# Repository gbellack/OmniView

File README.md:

#OmniView

##Hardware
--------
1. Texas Instruments CC3200 MCU

##Installation
1. You will need Code Composer Studio (CCS) version 6.1.1 installed on your computer. You can download this from TI's website. You will need to enter some credentials and get approved to be able to download the software.
2. You will be prompted to select modules that you want CCS to download. Please install the CC3200 package under SimpleLink Wifi Support tools.
3. After installing CCS, please install the CC3200 SDK from Texas Instruments.
4. If you launch Code Composer Studio for the first time, it will prompt you for a workspace directory. Feel free to pick a directory that you would like to work off.
5. Here comes the fun part. Please install GitHub for Windows. You will need this to pull the CCS project from this repository.  
// TODO

You should be able to build and run the project once all these are set up. 

###Flashing the program via UniFlash

If you would like to flash the program onto the Launchpad, you will need a seaparate program called Uniflash by Texas Instruments. Go ahead and download it from here and continue to follow the steps below. If you would not like to do so, you may skip them.
Credits to: [Texas Instruments Uniflash Wiki page](http://processors.wiki.ti.com/index.php/UniFlash_Quick_Start_Guide)

### Folder/File description
1. omniview/main.c : This is where the main program lies. All things related to scheduling is done here.

2. omniview/mode.c: This file contains the two modes that the facial recognition is capable of doing, as well as module initialization functions. All modules (display, camera etc.) are included and used here. Primary mode basically takes an image every second and returns the name of the person in the image.

3. omniview/pinmux.c/h : This is where we specify which pins are being used for certain protocols by the program.

4. omniview/modules folder: This stores all the modules/component libraries. More on that later...

5. omniview/modules/display/display.c/h: This file implements the driver for the display. It provides a good interface for the OLED display that we are using.

6. omniview/modules/display/buffer.c: This file contains the display buffer. The reason why we have this in a separate file is because the display had initialization values that we wanted to keep, and by adding this huge buffer definition in our display function, it will make that file really big and hard to read. Hence, we decided to split it into a separate file and link it up.

7. omniview/modules/display/font.c: This file contains the font settings for text on our OLED display. For the same reason above, we decided to move it to a separate file.

8. omniview/modules/interrupts/button_interrupt.c/h: These files contain interfaces for triggering a GPIO interrupt via one of our buttons. Some of the macros are linked to other macros defined by Texas Instruments.

9. omniview/modules/interrupts/timer_interrupt.c/h: These files contain interfaces for triggering a timer interrupt. This is mainly used by the microphone interface for audio recording purposes during secondary mode.

10. omniview/modules/microphone/microphone.c/h: These files contain the interfaces for the microphone.

11. omniview/modules/networking/tcp_network.c/h: These files contain the TCP networking interface required to send data/files across the network (or in our case, interact with our server).

12. omniview/modules/camera/mt9d111.c/h: These files contain the driver for the camera model that we are currently using.

13. omniview/modules/face_software/faceRec.cpp: This file contains the main server loop as well as several functions that help it in running.

14. omniview/modules/face_software/tcpClient.c/h: Houses the server side networking code used to communicate (by TCP) with the embedded device.

15. omniview/modules/face_software/wav_transcribe.py: Called by the main facial recognition loop. Communicates with google’s speech to text recognition server. Sends a string to parseName and receives names back. Sends names back to facial recognition main.

16. omniview/modules/face_software/parseName.py: Uses a natural language processing toolkit to process the string. Returns the names identified by the algorithm to wav_transcribe.

17. omniview/modules/face_software/training: Database holding our folders of faces. Test pic gets compared to this database to find the most similar face. A folder is created for each unique person in our dataset. The folder, named after the person, houses the pictures of the person inside.
Eg. omniview/modules/face_software/training/john_connolly/john1.jpg  is the first picture of John Connolly in the database.

###Speech Recognition
Please READ:
1. Make sure you have PyAudio installed.
2. All the examples are in the speech_recognition file.

###Version Control for Code Composer Studio Project
The .gitignore file on this repository should do the trick, but please:  
  
DO commit and push:  
1. .ccsproject  
2. .cproject  
3. .project  
4. .settings folder  
5. makefile.defs (if using SYS/BIOS)  

DO NOT commit and push:    
1. Release/*  
2. config/*  
3. .launches/  
4. .xdchelp  

Credits to: [Texas Instruments Wiki page](http://processors.wiki.ti.com/index.php/Source_control_with_CCS)  

##Support
Please feel free to contact any of us if you have any questions or concerns.

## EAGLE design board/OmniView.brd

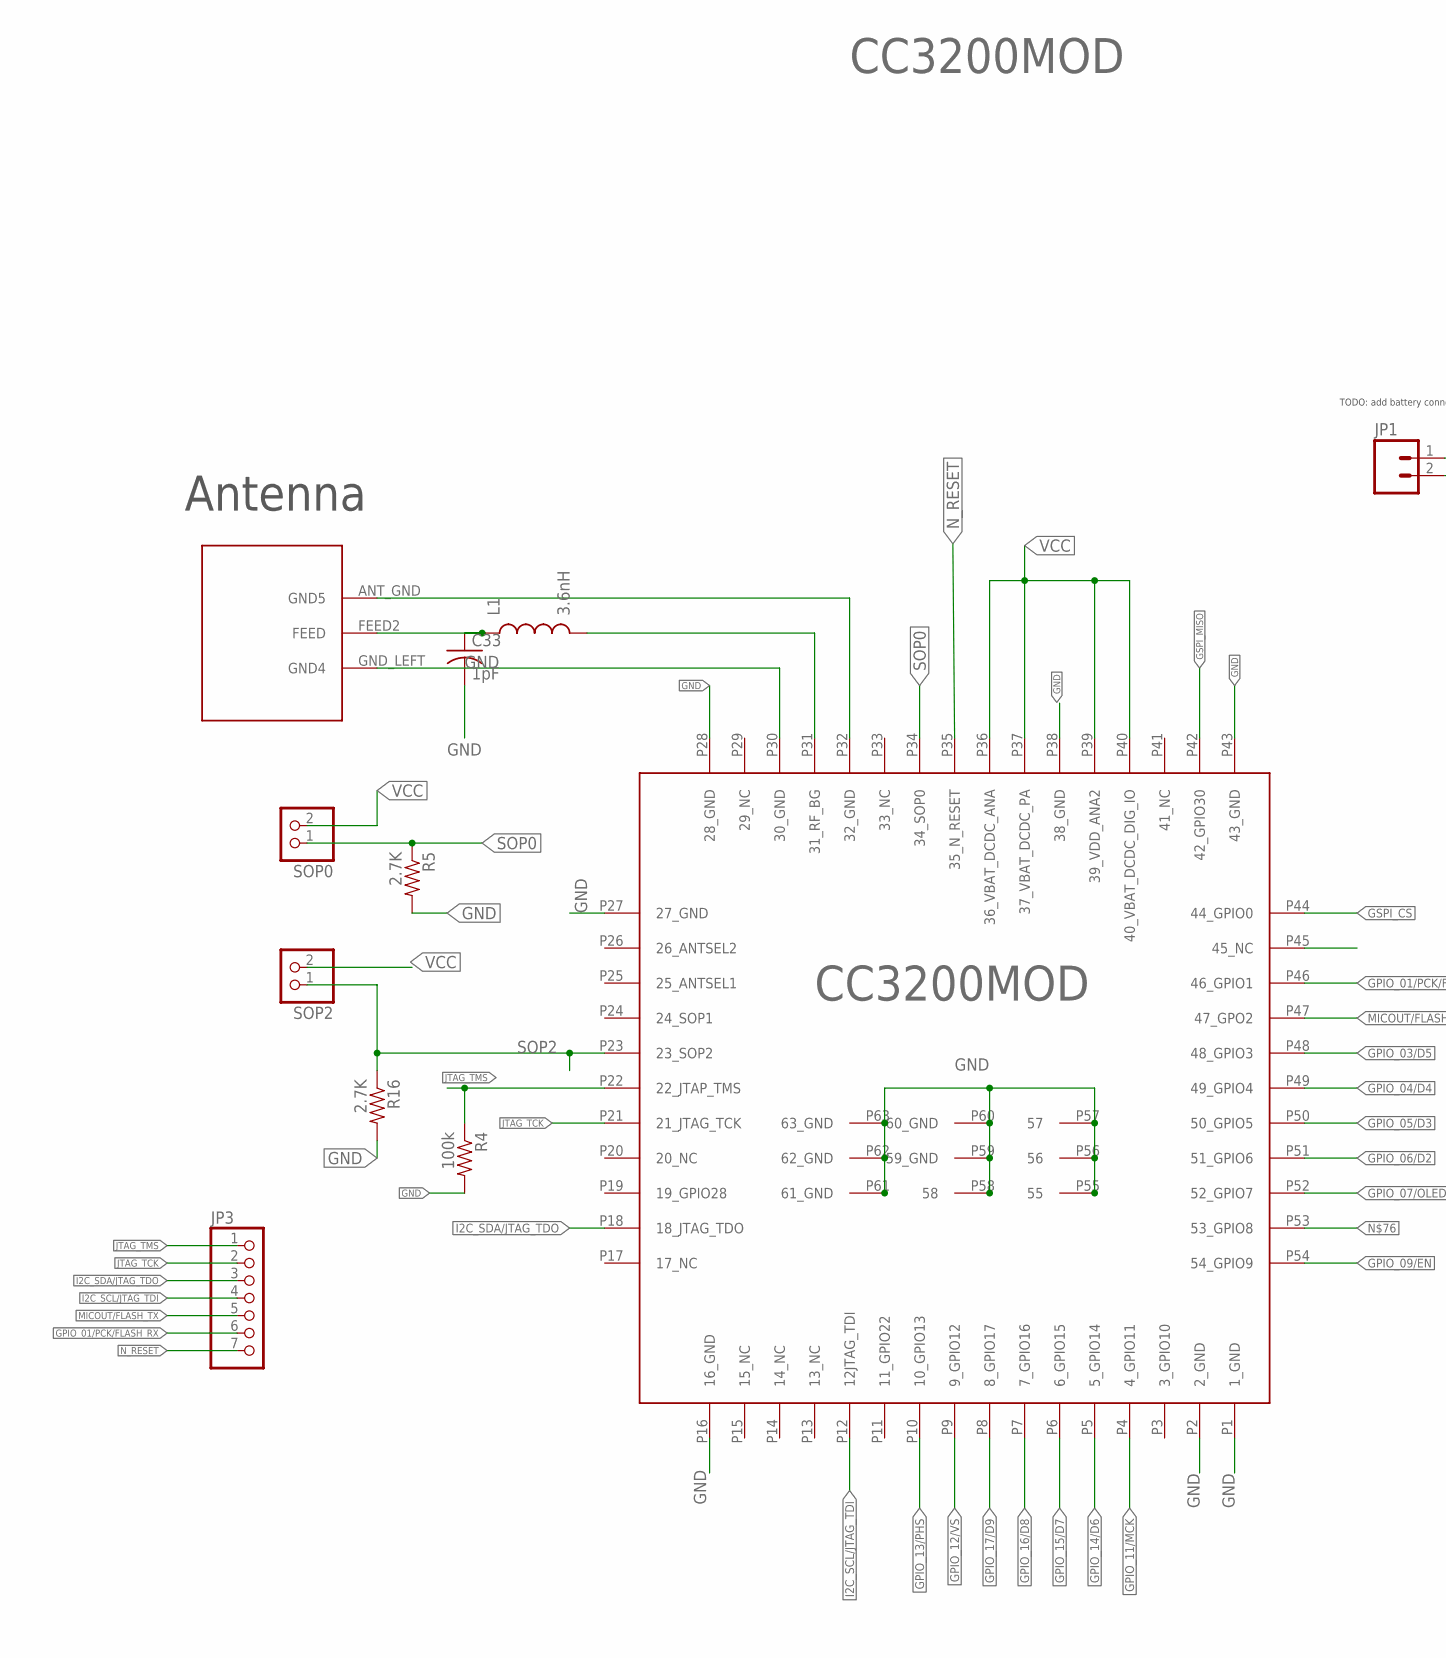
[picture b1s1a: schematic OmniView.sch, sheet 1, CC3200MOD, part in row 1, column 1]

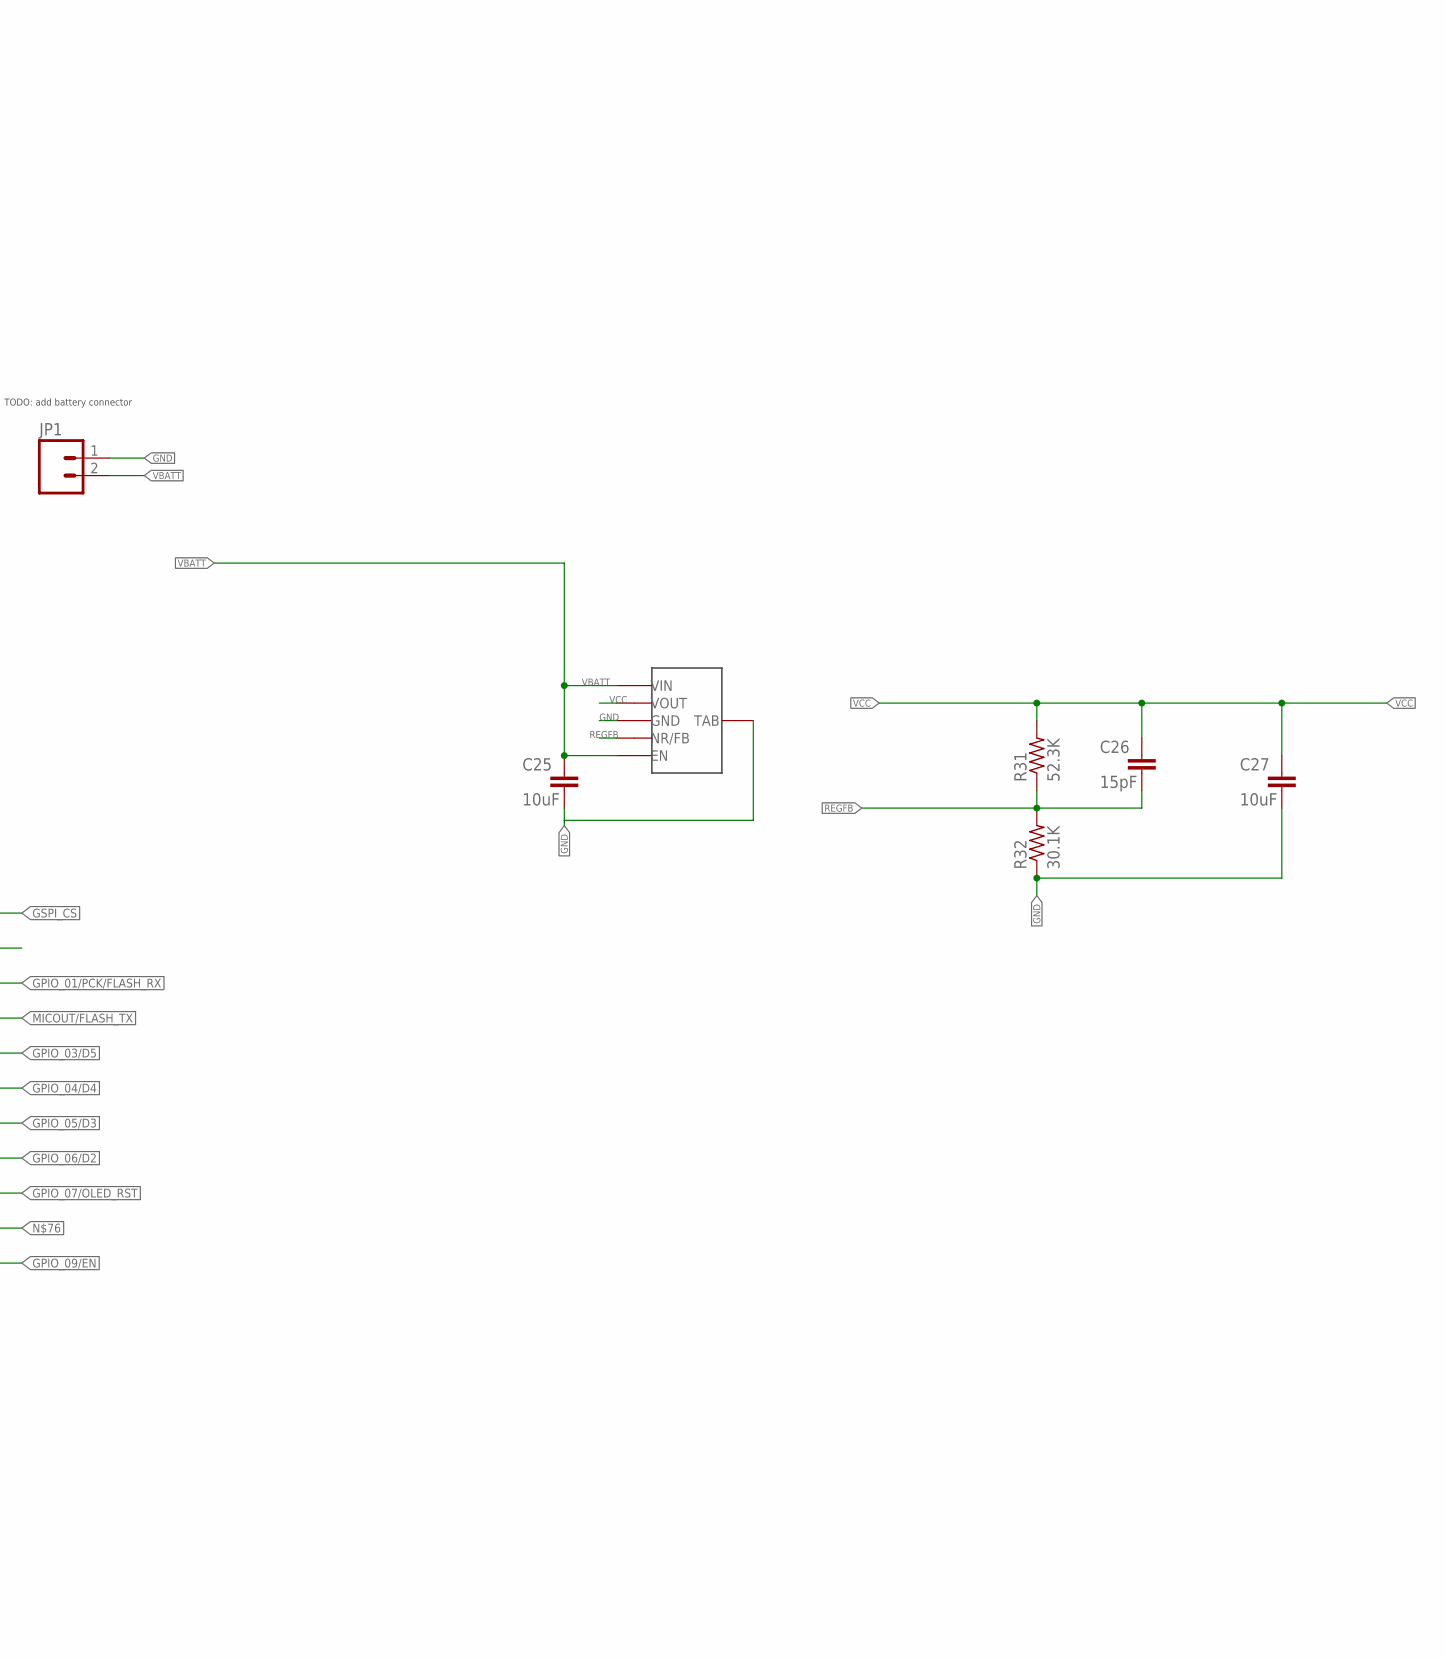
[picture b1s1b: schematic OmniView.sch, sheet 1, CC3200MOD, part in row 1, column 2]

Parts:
ANT_PAD: ANT
C25, C27: 10uF; C0603
C26: 15pF; C0603
C33: 1pF; C0402
CC3200MOD: CC3200; CC3200MOD
JP1: M02-JST-2MM-SMT; JST-2-SMD
JP3: PINHD-1X7; 1X07
L1: 3.6nH; C0402
R4: 100k; 0603-RES
R5, R16: 2.7K; 0603-RES
R31: 52.3K; R0805
R32: 30.1K; R0805
SOP0, SOP2: PINHD-1X2; 1X02
U$30: TPS737_DCQ

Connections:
GND: ANT_PAD.ANT_GND (GND5), ANT_PAD.GND_LEFT (GND4), C25.2, C27.2, C33.2, CC3200MOD.P1 (1_GND), CC3200MOD.P2 (2_GND), CC3200MOD.P16 (16_GND), CC3200MOD.P27 (27_GND), CC3200MOD.P28 (28_GND), CC3200MOD.P30 (30_GND), CC3200MOD.P32 (32_GND), CC3200MOD.P38 (38_GND), CC3200MOD.P43 (43_GND), CC3200MOD.P55 (55), CC3200MOD.P56 (56), CC3200MOD.P57 (57), CC3200MOD.P58 (58), CC3200MOD.P59 (59_GND), CC3200MOD.P60 (60_GND), CC3200MOD.P61 (61_GND), CC3200MOD.P62 (62_GND), CC3200MOD.P63 (63_GND), JP1.1 (2), R4.2, R5.2, R16.2, R32.1, U$30.GND, U$30.TAB; also elsewhere on the board
GPIO_01/PCK/FLASH_RX: CC3200MOD.P46 (46_GPIO1); also elsewhere on the board
GPIO_03/D5: CC3200MOD.P48 (48_GPIO3); also elsewhere on the board
GPIO_04/D4: CC3200MOD.P49 (49_GPIO4); also elsewhere on the board
GPIO_05/D3: CC3200MOD.P50 (50_GPIO5); also elsewhere on the board
GPIO_06/D2: CC3200MOD.P51 (51_GPIO6); also elsewhere on the board
GPIO_07/OLED_RST: CC3200MOD.P52 (52_GPIO7)
GPIO_09/EN: CC3200MOD.P54 (54_GPIO9); also elsewhere on the board
GPIO_11/MCK: CC3200MOD.P4 (4_GPIO11); also elsewhere on the board
GPIO_12/VS: CC3200MOD.P9 (9_GPIO12); also elsewhere on the board
GPIO_13/PHS: CC3200MOD.P10 (10_GPIO13); also elsewhere on the board
GPIO_14/D6: CC3200MOD.P5 (5_GPIO14); also elsewhere on the board
GPIO_15/D7: CC3200MOD.P6 (6_GPIO15); also elsewhere on the board
GPIO_16/D8: CC3200MOD.P7 (7_GPIO16); also elsewhere on the board
GPIO_17/D9: CC3200MOD.P8 (8_GPIO17); also elsewhere on the board
GSPI_CS: CC3200MOD.P44 (44_GPIO0)
GSPI_MISO: CC3200MOD.P42 (42_GPIO30)
I2C_SCL/JTAG_TDI: CC3200MOD.P12 (12JTAG_TDI), JP3.4; also elsewhere on the board
I2C_SDA/JTAG_TDO: CC3200MOD.P18 (18_JTAG_TDO), JP3.3; also elsewhere on the board
JTAG_TCK: CC3200MOD.P21 (21_JTAG_TCK), JP3.2
JTAG_TMS: CC3200MOD.P22 (22_JTAP_TMS), JP3.1, R4.1
MCU_RF: CC3200MOD.P31 (31_RF_BG), L1.2
MICOUT/FLASH_TX: CC3200MOD.P47 (47_GPO2), JP3.5; also elsewhere on the board
unnamed: ANT_PAD.FEED2 (FEED), C33.1, L1.1
N_RESET: CC3200MOD.P35 (35_N_RESET), JP3.7
REGFB: C26.2, R31.1, R32.2, U$30.NR/FB
SOP0: CC3200MOD.P34 (34_SOP0), R5.1, SOP0.1
SOP2: CC3200MOD.P23 (23_SOP2), R16.1, SOP2.1
VBATT: C25.1, JP1.2 (1), U$30.EN, U$30.IN (VIN)
VCC: C26.1, C27.1, CC3200MOD.P36 (36_VBAT_DCDC_ANA), CC3200MOD.P37 (37_VBAT_DCDC_PA), CC3200MOD.P39 (39_VDD_ANA2), CC3200MOD.P40 (40_VBAT_DCDC_DIG_IO), R31.2, SOP0.2, SOP2.2, U$30.OUT (VOUT); also elsewhere on the board

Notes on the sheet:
Antenna
TODO: add battery connector

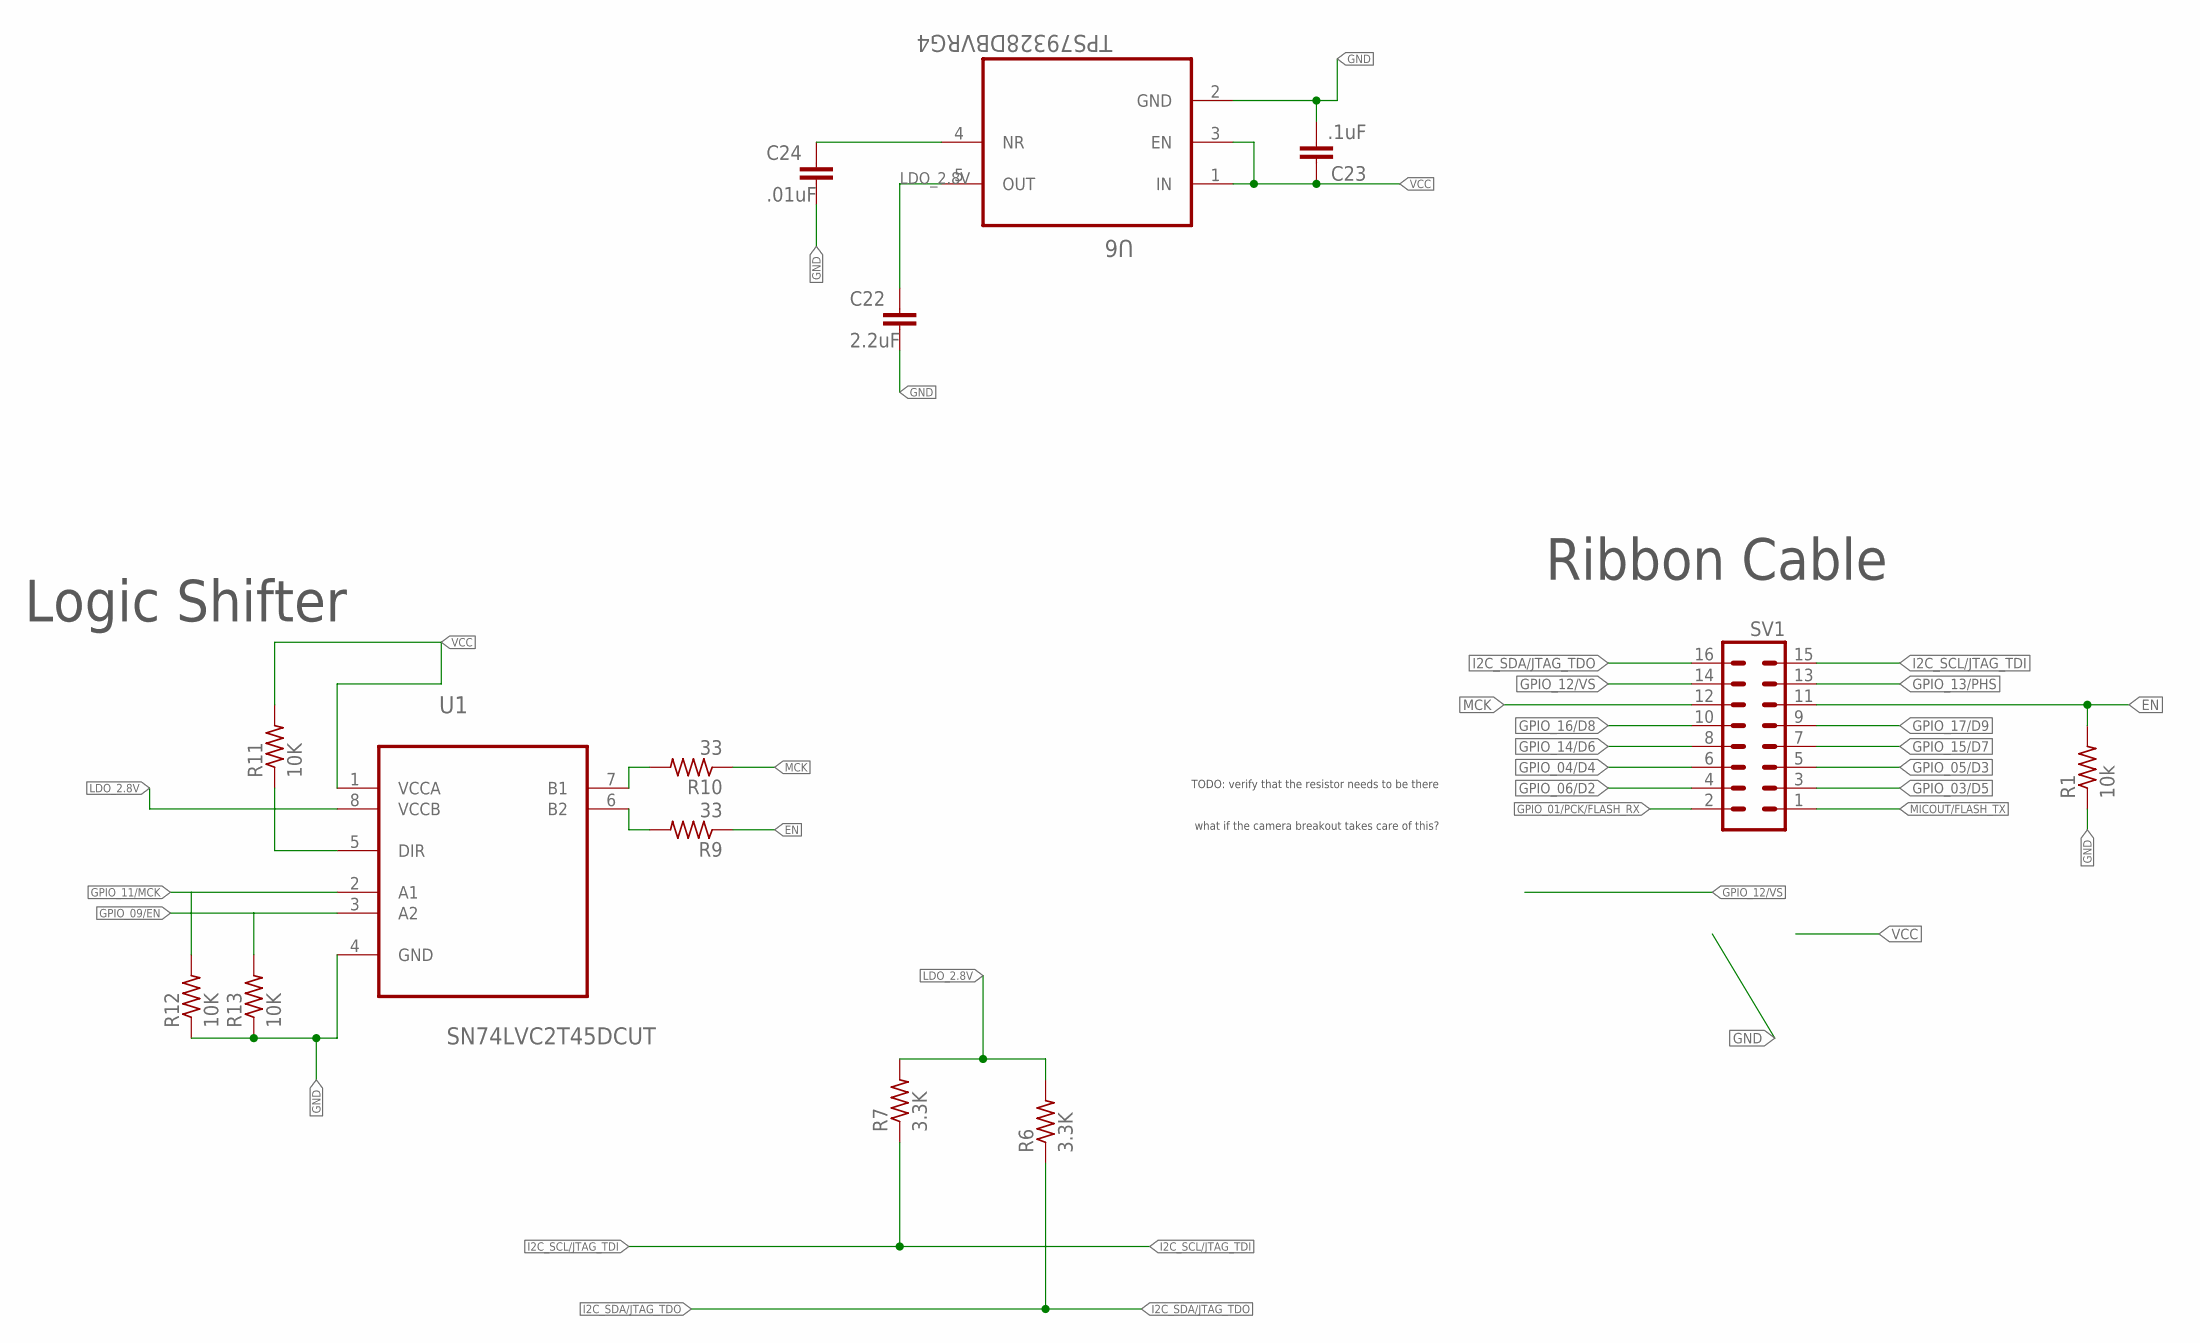
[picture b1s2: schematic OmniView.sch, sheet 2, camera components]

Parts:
C22: 2.2uF; C0603
C23: .1uF; C0603
C24: .01uF; C0603
R1: 10k; R0603
R6, R7: 3.3K; R0603
R9, R10: 33; R0603
R11, R12, R13: 10K; R0603
SV1: 16P
U1: SN74LVC2T45DCUT; SOP50P310X90-8N
U6: TPS79328DBVRG4; SOT95P280X145-5N

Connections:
EN: R1.2, R9.1, SV1.11
GND: C22.2, C23.2, C24.2, R1.1, R12.1, R13.1, U1.4 (GND), U6.2 (GND); also elsewhere on the board
GPIO_01/PCK/FLASH_RX: SV1.2; also elsewhere on the board
GPIO_03/D5: SV1.3; also elsewhere on the board
GPIO_04/D4: SV1.6; also elsewhere on the board
GPIO_05/D3: SV1.5; also elsewhere on the board
GPIO_06/D2: SV1.4; also elsewhere on the board
GPIO_09/EN: R13.2, U1.3 (A2); also elsewhere on the board
GPIO_11/MCK: R12.2, U1.2 (A1); also elsewhere on the board
GPIO_12/VS: SV1.14; also elsewhere on the board
GPIO_13/PHS: SV1.13; also elsewhere on the board
GPIO_14/D6: SV1.8; also elsewhere on the board
GPIO_15/D7: SV1.7; also elsewhere on the board
GPIO_16/D8: SV1.10; also elsewhere on the board
GPIO_17/D9: SV1.9; also elsewhere on the board
I2C_SCL/JTAG_TDI: R7.1, SV1.15; also elsewhere on the board
I2C_SDA/JTAG_TDO: R6.1, SV1.16; also elsewhere on the board
LDO_2.8V: C22.1, R6.2, R7.2, U1.8 (VCCB), U6.5 (OUT)
MCK: R10.1, SV1.12
MICOUT/FLASH_TX: SV1.1; also elsewhere on the board
unnamed: R11.1, U1.5 (DIR)
unnamed: C24.1, U6.4 (NR)
unnamed: R10.2, U1.7 (B1)
unnamed: R9.2, U1.6 (B2)
VCC: C23.1, R11.2, U1.1 (VCCA), U6.1 (IN), U6.3 (EN); also elsewhere on the board

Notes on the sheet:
Ribbon Cable
Logic Shifter
what if the camera breakout takes care of this?
TODO: verify that the resistor needs to be there

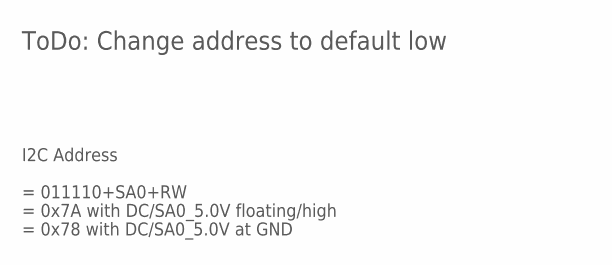
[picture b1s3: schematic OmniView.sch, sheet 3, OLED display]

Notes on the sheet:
= 011110+SA0+RW
= 0x7A with DC/SA0_5.0V floating/high
= 0x78 with DC/SA0_5.0V at GND
I2C Address
ToDo: Change address to default low

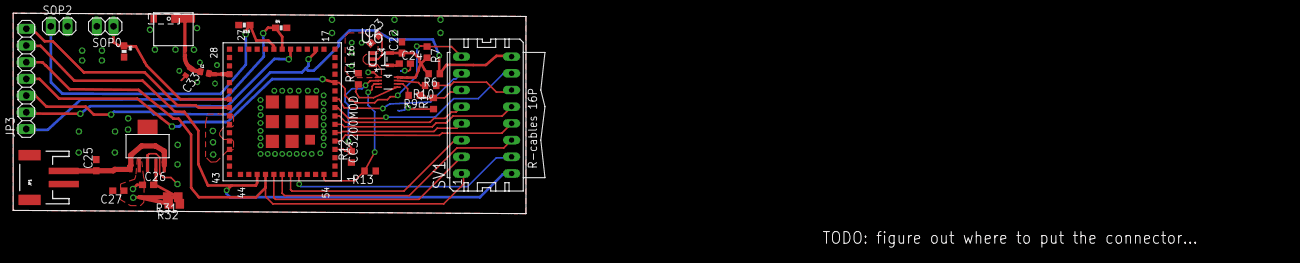
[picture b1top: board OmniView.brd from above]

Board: 4 copper layers, 193.7 x 36.1 mm, 31 parts (0 on the bottom side), 34 nets.

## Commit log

2015-10-03 Initial test code+pics for openBR
2015-10-03 working code and compiles on Loren's machine
2015-10-03 Added more pics
2015-10-03 more pics
2015-10-03 slightly updated code
2015-10-03 added datasheets
2015-10-03 moar faces
2015-10-03 another pic
2015-10-03 multiple face detection somewhat working
2015-10-04 cleaned up directory
2015-10-10 eagle initial commit
    initial eagle schematic commit. For now just contains the footprints of
    our devices. Still need to make power regulator.
2015-10-11 schematic check-up
    did a little bit of schematic setting up
2015-10-11 multiple faces working?
2015-10-11 test pics
2015-10-12 Added 1 more datasheet
2015-10-12 :space_invader: Added .gitattributes
2015-10-12 added gitignore
2015-10-12 added CCS project
2015-10-14 wireless ap is working
2015-10-14 fixed README
2015-10-14 i hope it works now
2015-10-14 Added module header and source files
2015-10-15 moved facial rec stuff
2015-10-15 shifted face rec stuff
2015-10-16 wireless module is working
2015-10-18 organized libraries into module folders
2015-10-19 added adafruit drivers
2015-10-21 schematic check-up
    initial schematic done, beginning routing
2015-10-22 added display driver, not sure if working yet
2015-10-23 added better display drivers
2015-10-23 display is showing something
2015-10-24 initial board push
    first revision of board is...done! This revision still needs to:
    -review antenna trace with expert
    -clean up some of the routing
    -be reviewed by non-john member of the team
2015-10-31 display still has 1 more bug
2015-11-02 added Arduino display module library
2015-11-02 separated buffer and font into c files
2015-11-04 added some networking interface to the repo
2015-11-04 cleaned up code
2015-11-05 display DONE
2015-11-05 cleaned up code and fixed i2c to use pin 16 & 17
2015-11-05 not sure if it works
2015-11-06 added camera code but cant compile
2015-11-06 builds ?
2015-11-08 small camera integration changes
2015-11-08 added project proposal
2015-11-08 cleaner, but doesn't work yet
2015-11-09 this is working
2015-11-09 added ccxml file
2015-11-12 freeRTOS tasks are now done
2015-11-12 fixed hard fault bug
2015-11-12 changed display interface
2015-11-12 connected tcp to camera
2015-11-13 reverted screen
2015-11-13 added speech recognition samples
2015-11-13 excluded speech recognition from build
2015-11-15 First attempt at integrating camera, networking, and display. This commit is broken and can't get through the initModules
2015-11-15 prior merge not done properly, fixed
2015-11-15 Still trying to get just camera working
2015-11-15 Camera+Networking works, except when diplay attached (even if display software not called)
2015-11-19 added button interrupt code
2015-11-19 added better descriptions for the button and microphone interrupt
2015-11-21 display glitch fix
    added reset for i2c glitch fix, and also added glitch tolerance on the
    i2c bus
2015-11-22 removed a few delays. Currently having issues running the primary loop for a long time. Will crash undeterministically after a while by going to prvTaskExitError
2015-11-24 Still trying to debug the loop crashing. Narrowed it down and have debugging implemented
2015-11-29 added timer interrupt interface
2015-12-01 STABLE. Fixed networking bug. Primary mode runs infinitly now
2015-12-01 Integrated button interrupt code
2015-12-02 Added networking flag functionality to differntiate between query and add requests
2015-12-02 microphone impl
    added code for grabbing 'x' seconds of data from the microphone
2015-12-02 server side code
2015-12-02 updated display reset pin to PCB pinout
2015-12-03 Added infrastructure for secondary mode and integrated button and mic code. Currently button interrupts are not triggering and mic code is untested
2015-12-04 STABLE. All code for primary and secondary modes incorrporated and working.
2015-12-05 changed camera intialization and added debug information
2015-12-05 PCB changes
    added some small changes for migrating from dev board to PCB
2015-12-06 STABLE. Primary mode up and running perfectly on the pcb!
2015-12-10 updated display offset for PCB
2015-12-10 fixed indent bug for display
2015-12-10 Added possible restart fix. Untested
2015-12-14 server side stuff
2015-12-15 added pdf files

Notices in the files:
parts and their libraries:
SparkFun-Resistors: Licensing: Creative Commons ShareAlike 4.0 International - https://creativecommons.org/licenses/by-sa/4.0
